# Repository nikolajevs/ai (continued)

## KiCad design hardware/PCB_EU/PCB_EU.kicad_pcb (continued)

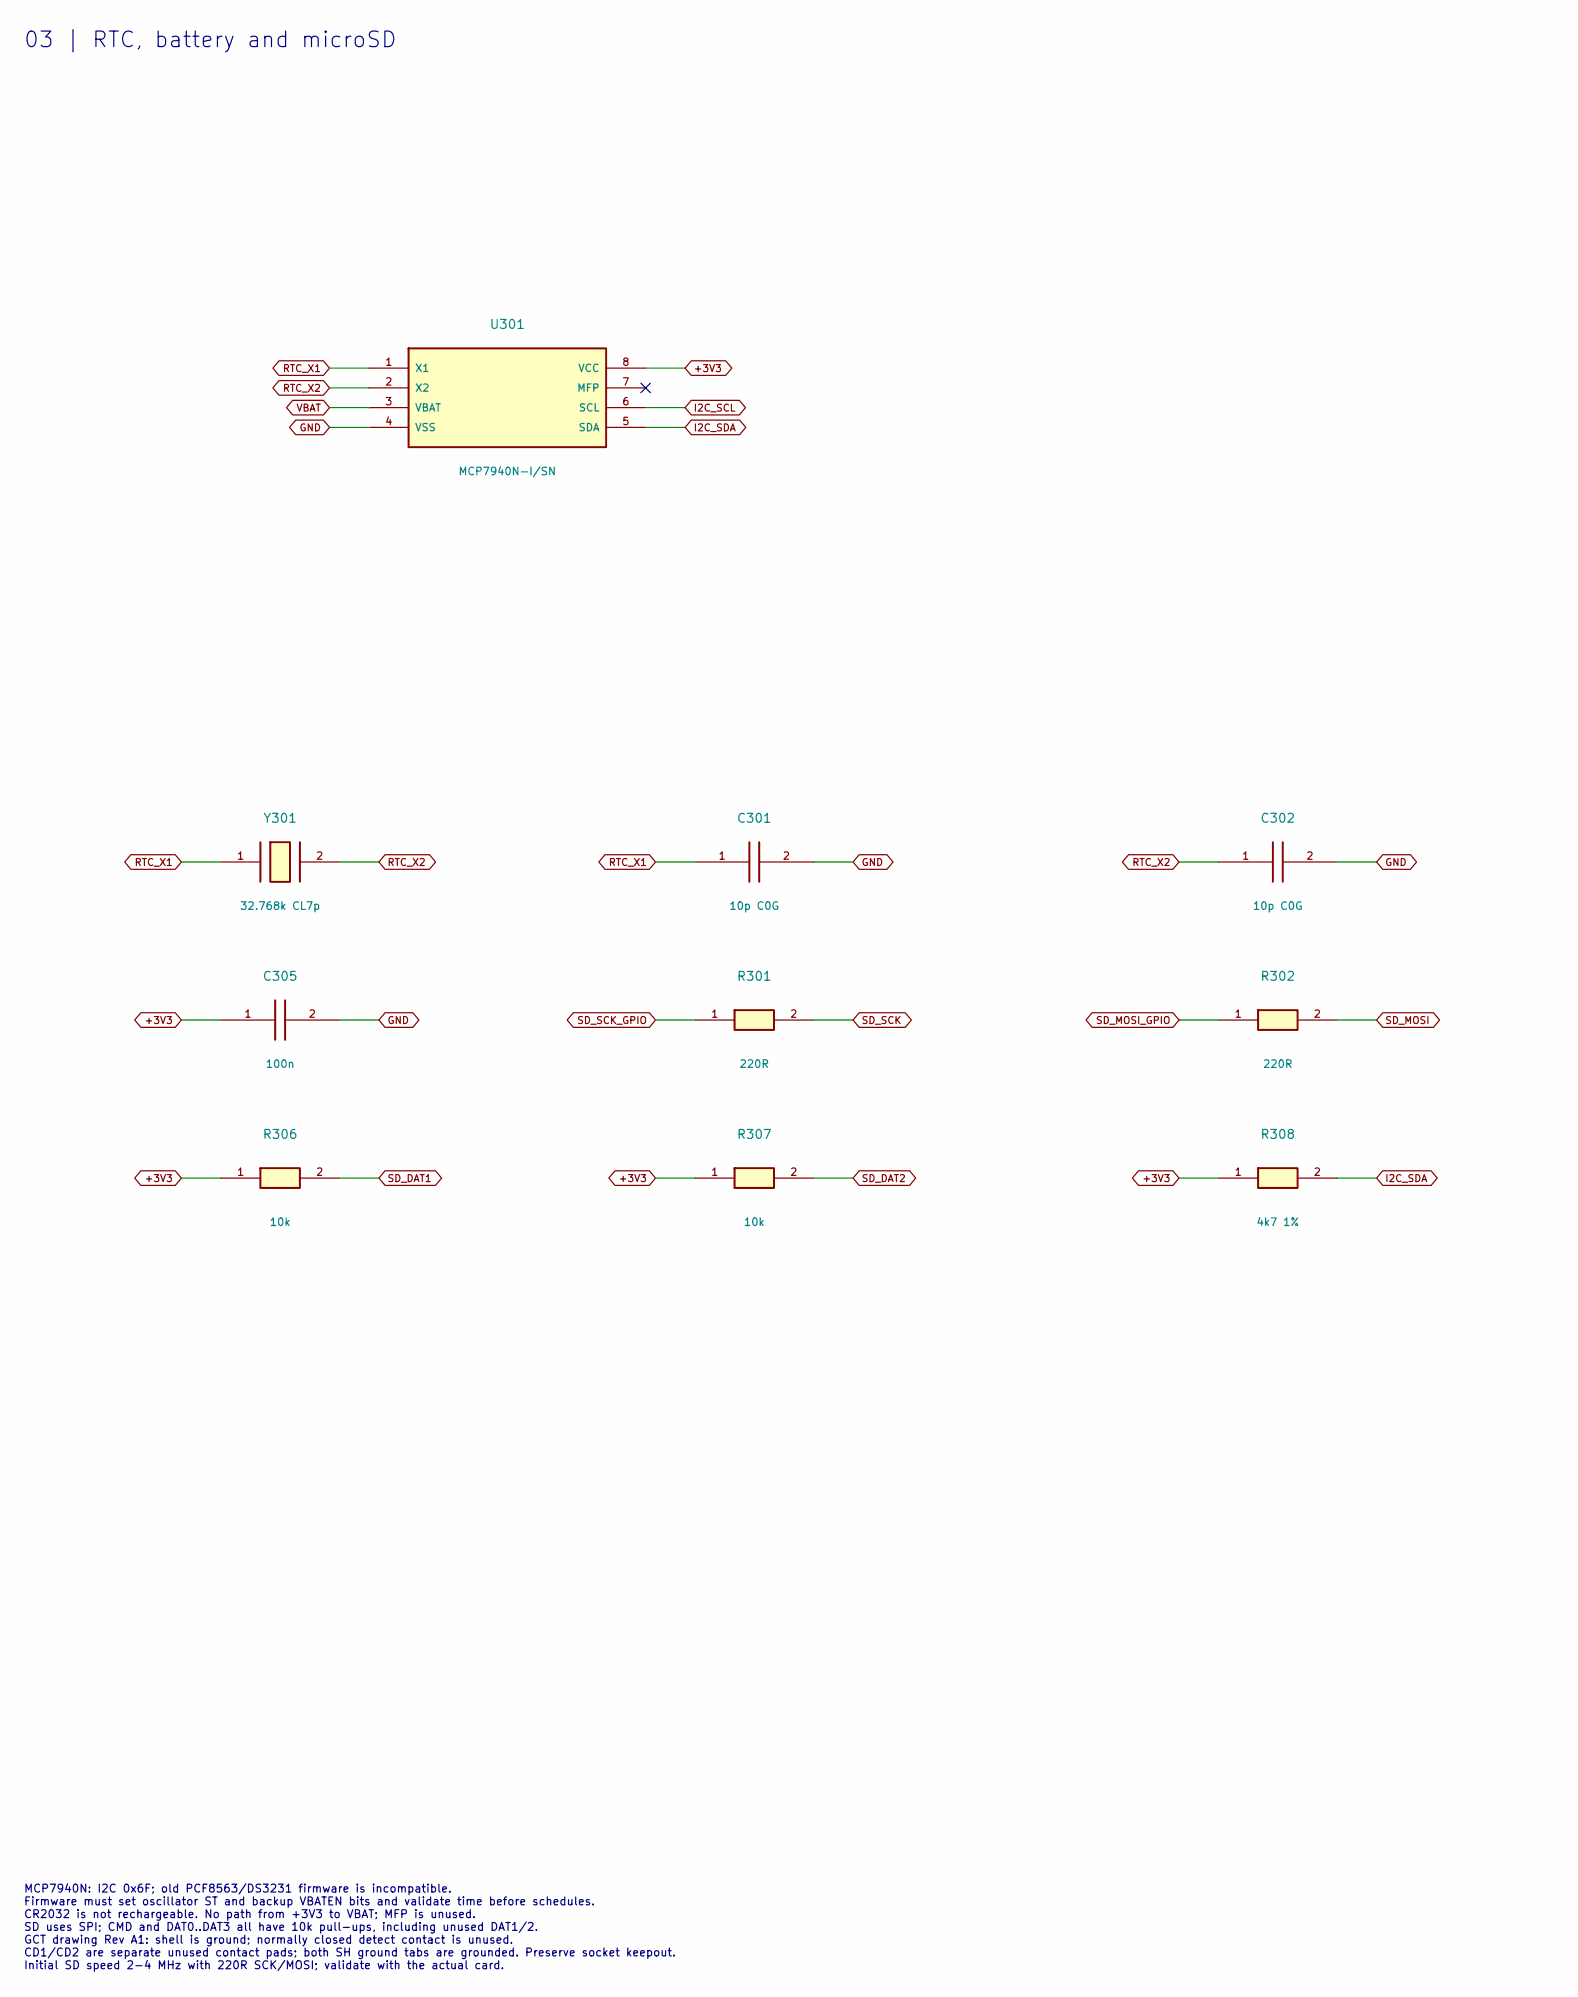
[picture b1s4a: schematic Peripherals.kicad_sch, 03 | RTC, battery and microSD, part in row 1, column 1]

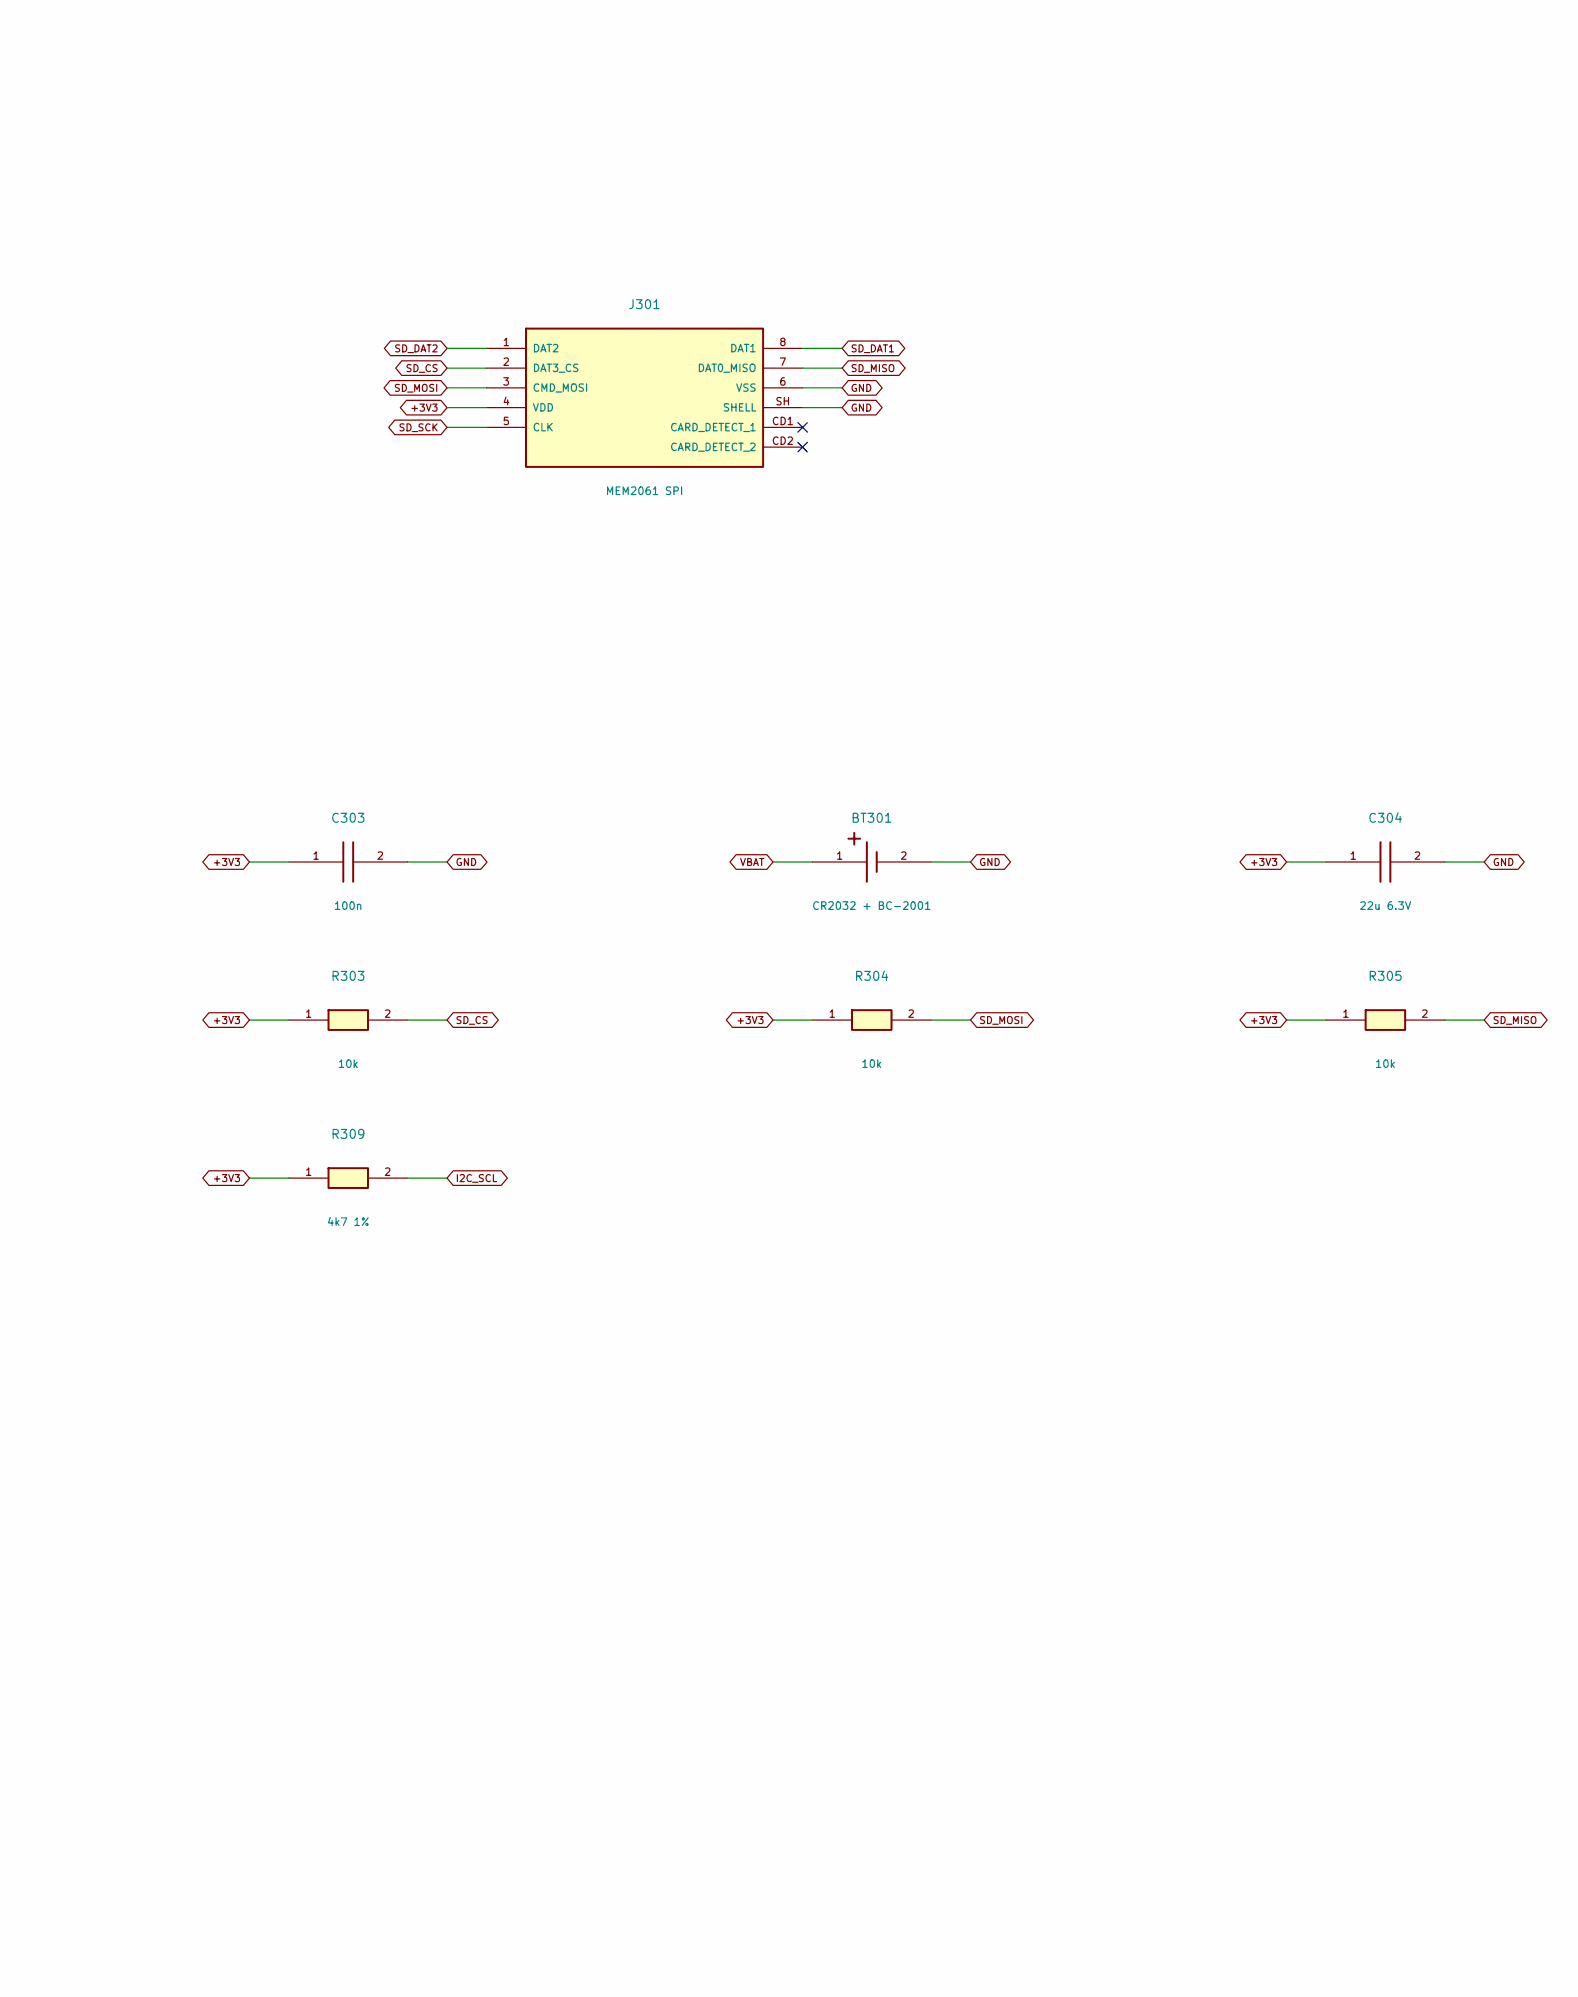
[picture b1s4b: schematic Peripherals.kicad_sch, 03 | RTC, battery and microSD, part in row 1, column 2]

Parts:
BT301: CR2032 + BC-2001; Battery_COMF_BC-2001; MPN BC-2001
C301, C302: 10p C0G; C_1206_3216Metric; MPN C1206C100J5GACTU
C303, C305: 100n; C_0805_2012Metric; MPN CL21B104KBCNNNC
C304: 22u 6.3V; C_1206_3216Metric; MPN CL31A226KQHNNNE
J301: MEM2061 SPI; microSD_GCT_MEM2061-01-188-00-A; MPN MEM2061-01-188-00-A
R301, R302: 220R; R_1206_3216Metric; MPN SMD1206-220R-1%
R303, R304, R305, R306, R307: 10k; R_0603_1608Metric; MPN SMD0603-10K
R308, R309: 4k7 1%; R_1206_3216Metric; MPN SMD1206 4K7 1%
U301: MCP7940N-I/SN; SOIC-8_3.9x4.9mm_P1.27mm; MPN MCP7940N-I/SN
Y301: 32.768k CL7p; Crystal_Abracon_ABS07; MPN ABS07-32.768KHZ-7-T

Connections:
+3V3: C303.1, C304.1, C305.1, J301.4 (VDD), R303.1, R304.1, R305.1, R306.1, R307.1, R308.1, R309.1, U301.8 (VCC); also elsewhere on the board
GND: BT301.2, C301.2, C302.2, C303.2, C304.2, C305.2, J301.6 (VSS), J301.SH (SHELL), U301.4 (VSS); also elsewhere on the board
I2C_SCL: R309.2, U301.6 (SCL); also elsewhere on the board
I2C_SDA: R308.2, U301.5 (SDA); also elsewhere on the board
RTC_X1: C301.1, U301.1 (X1), Y301.1
RTC_X2: C302.1, U301.2 (X2), Y301.2
SD_CS: J301.2 (DAT3_CS), R303.2; also elsewhere on the board
SD_DAT1: J301.8 (DAT1), R306.2
SD_DAT2: J301.1 (DAT2), R307.2
SD_MISO: J301.7 (DAT0_MISO), R305.2; also elsewhere on the board
SD_MOSI: J301.3 (CMD_MOSI), R302.2, R304.2
SD_MOSI_GPIO: R302.1; also elsewhere on the board
SD_SCK: J301.5 (CLK), R301.2
SD_SCK_GPIO: R301.1; also elsewhere on the board
VBAT: BT301.1, U301.3 (VBAT)

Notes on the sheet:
03 | RTC, battery and microSD
MCP7940N: I2C 0x6F; old PCF8563/DS3231 firmware is incompatible. Firmware must set oscillator ST and backup VBATEN bits and validate time before schedules. CR2032 is not rechargeable. No path from +3V3 to VBAT; MFP is unused. SD uses SPI; CMD and DAT0..DAT3 all have 10k pull-ups, including unused D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

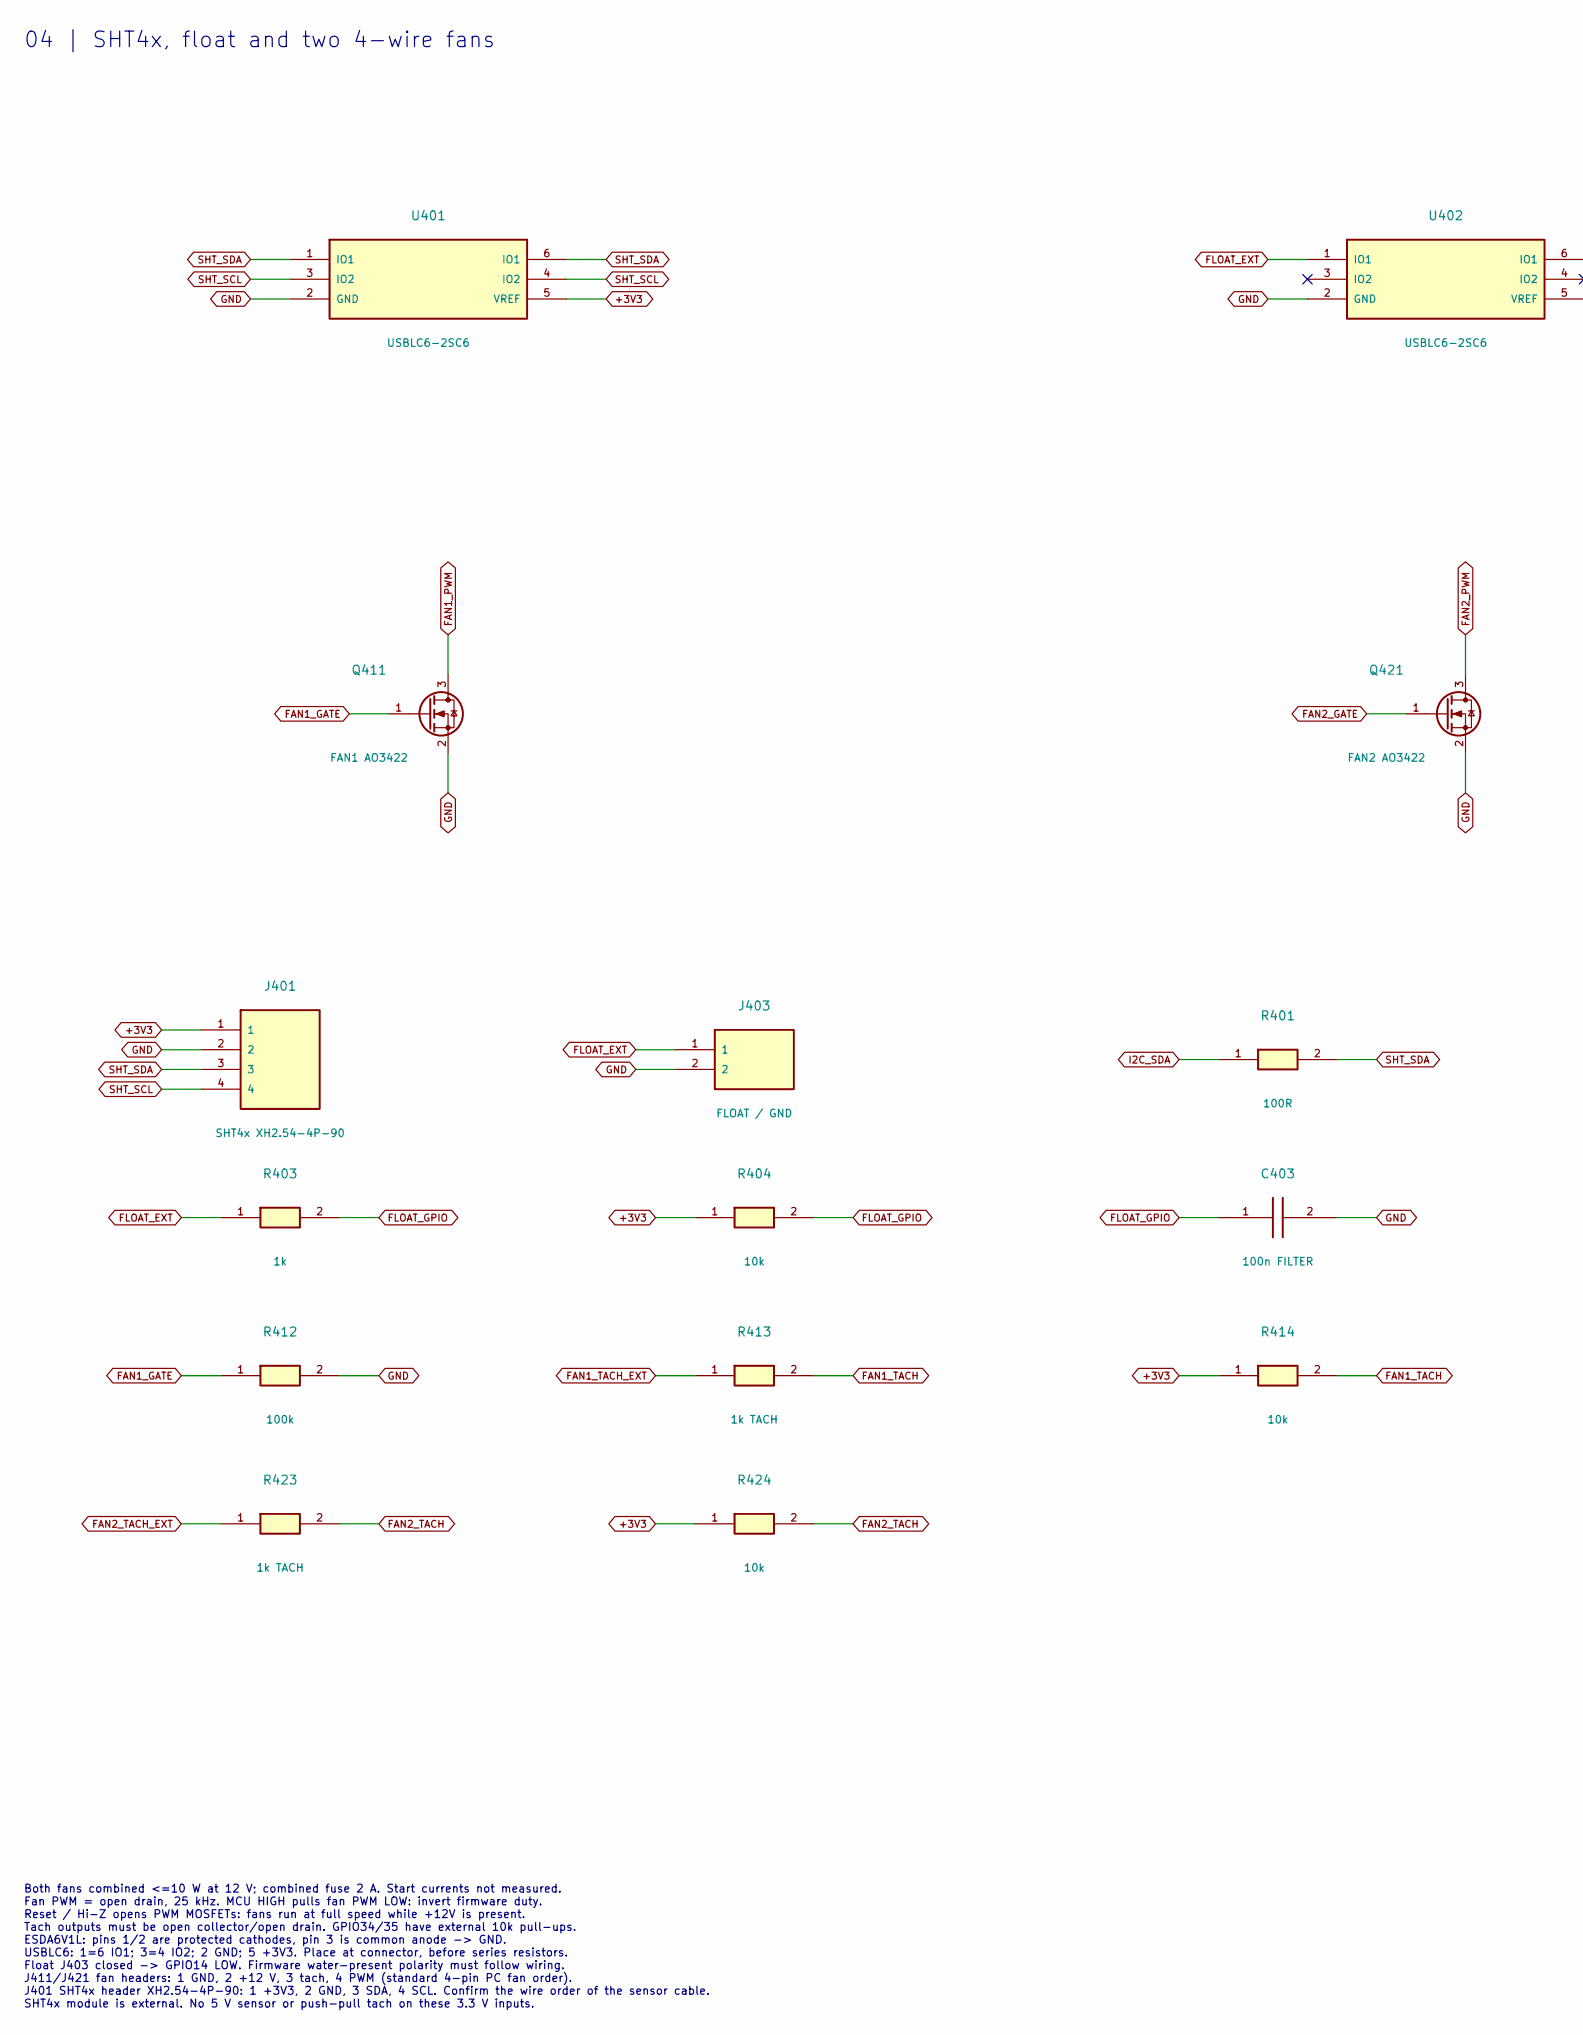
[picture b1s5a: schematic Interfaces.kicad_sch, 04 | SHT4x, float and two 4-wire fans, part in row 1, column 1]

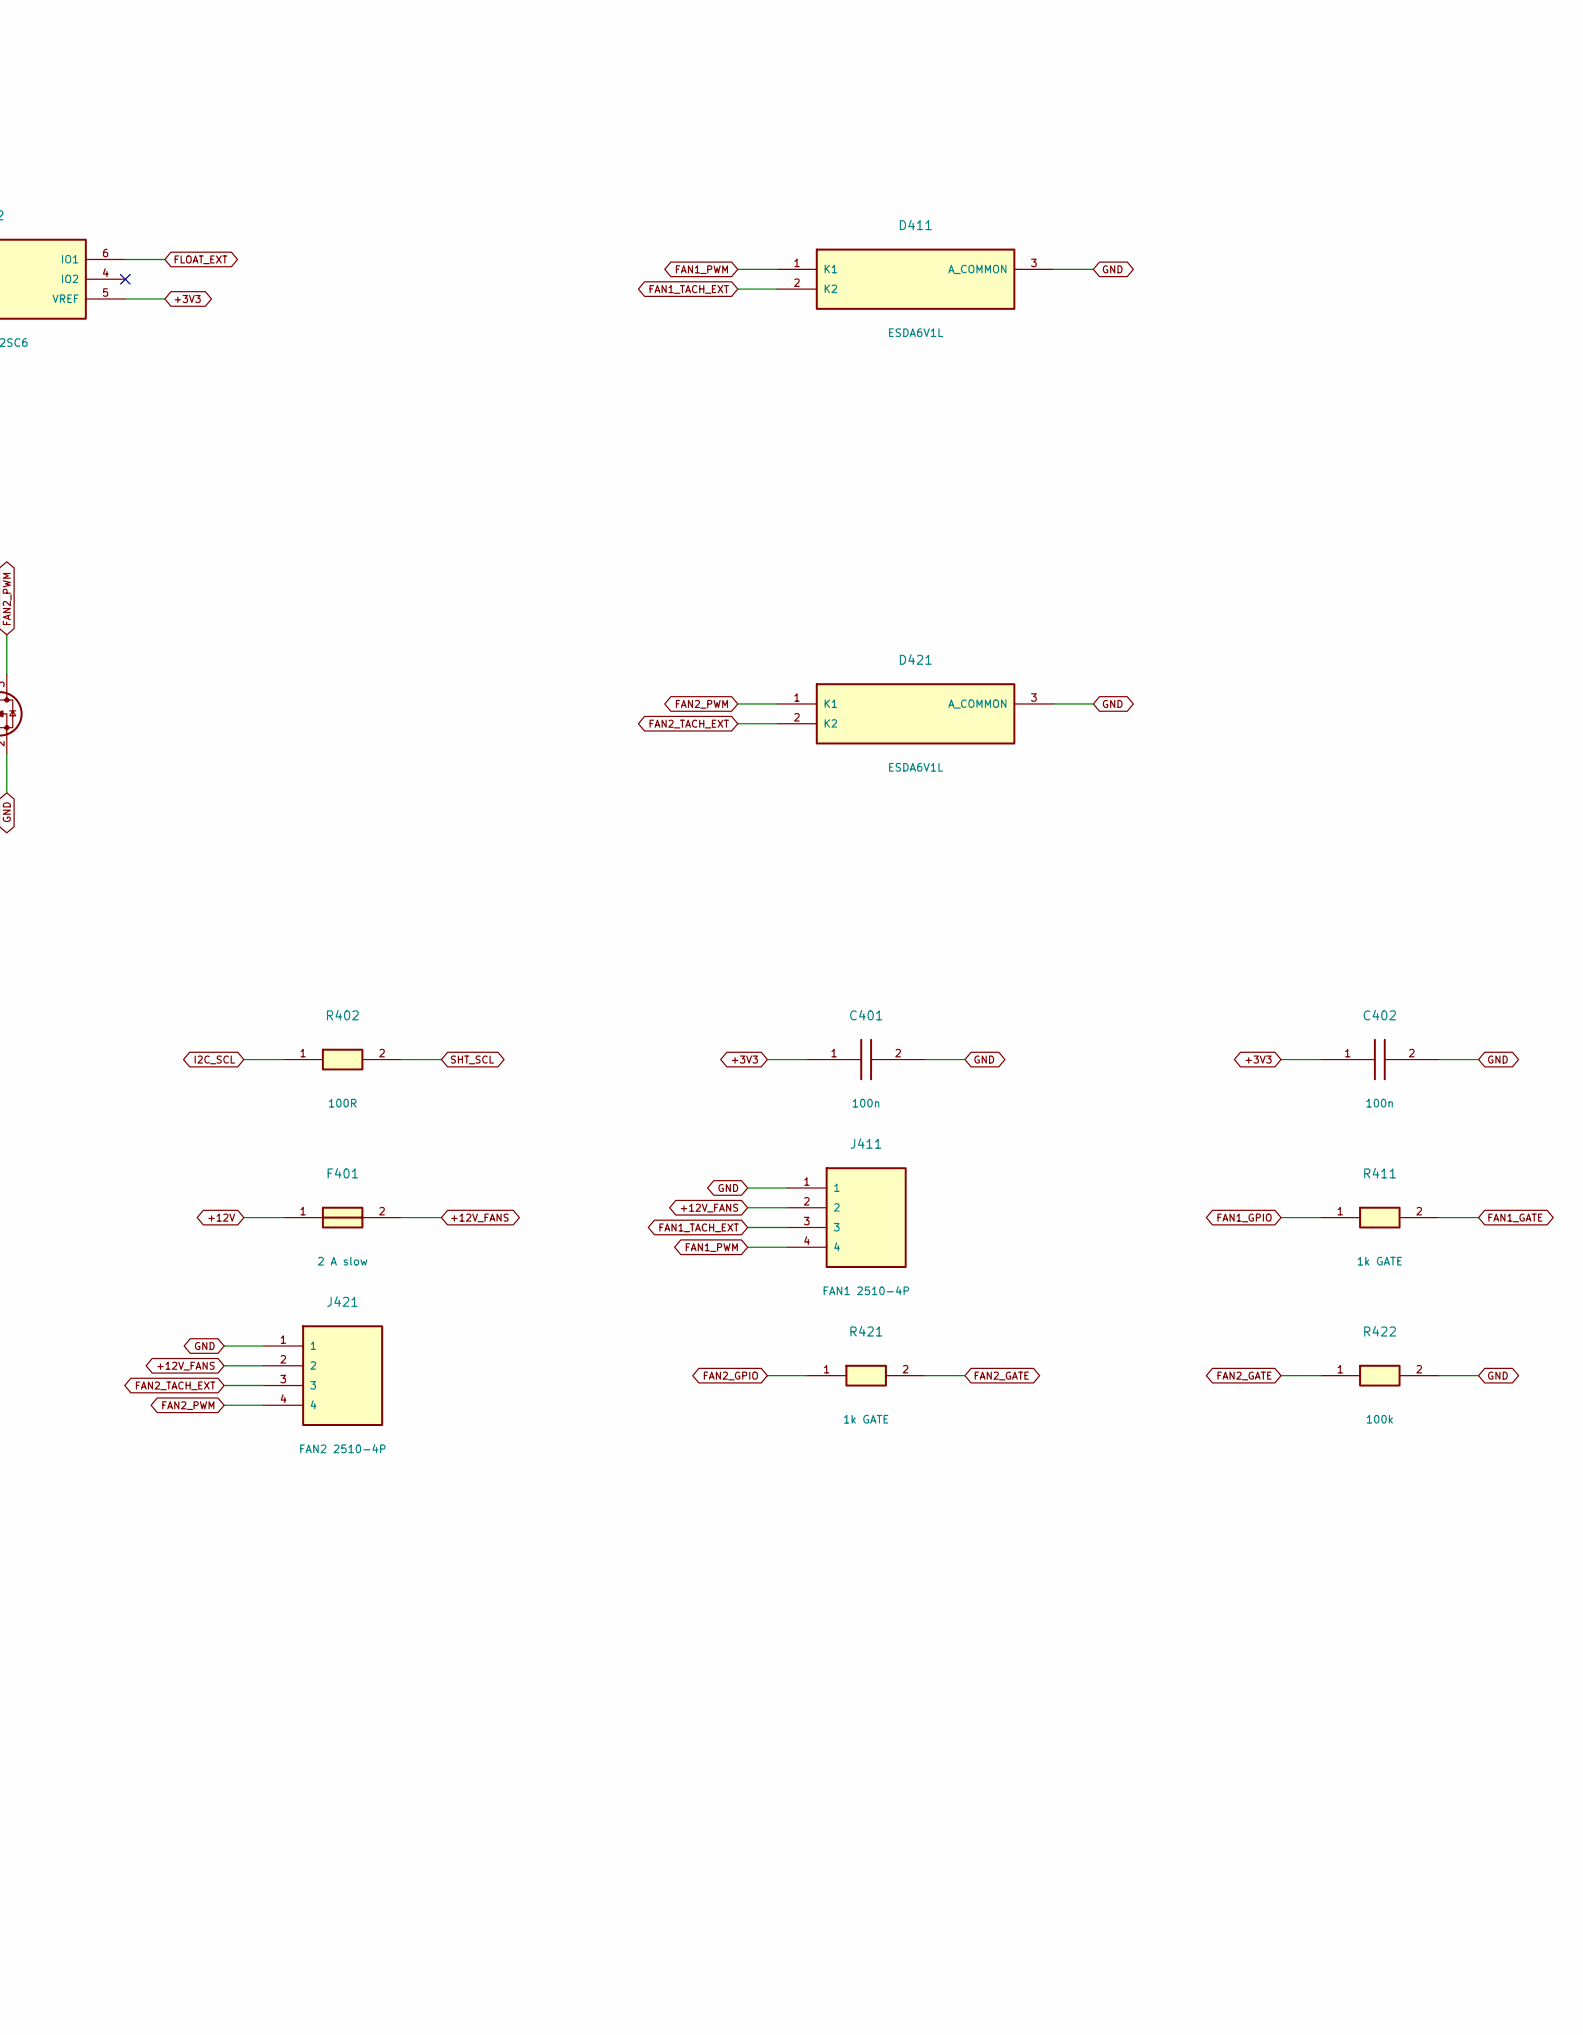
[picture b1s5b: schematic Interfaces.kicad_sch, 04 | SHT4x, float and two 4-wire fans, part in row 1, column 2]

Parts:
C401, C402: 100n; C_0805_2012Metric; MPN CL21B104KBCNNNC
C403: 100n FILTER; C_0805_2012Metric; MPN CL21B104KBCNNNC
D411, D421: ESDA6V1L; SOT-23; MPN ESDA6V1L
F401: 2 A slow; Fuse_Schurter_UMT250; MPN 3403.0169.11
J401: SHT4x XH2.54-4P-90; JST_XH_S4B-XH-A_1x04_P2.50mm_Horizontal; MPN XH2.54-4P-90
J403: FLOAT / GND; TerminalBlock_Degson_DG306-5.0_1x02; MPN DG306-5.0-2P12
J411: FAN1 2510-4P; Molex_KK-254_AE-6410-04A_1x04_P2.54mm_Vertical; MPN KF2510-4A
J421: FAN2 2510-4P; Molex_KK-254_AE-6410-04A_1x04_P2.54mm_Vertical; MPN KF2510-4A
Q411: FAN1 AO3422; SOT-23; MPN AO3422
Q421: FAN2 AO3422; SOT-23; MPN AO3422
R401, R402: 100R; R_1206_3216Metric; MPN SMD1206-100R-1%
R403: 1k; R_0603_1608Metric; MPN SMD0603-1K
R404, R414, R424: 10k; R_0603_1608Metric; MPN SMD0603-10K
R411, R421: 1k GATE; R_0603_1608Metric; MPN SMD0603-1K
R412, R422: 100k; R_0603_1608Metric; MPN SMD0603-100K
R413, R423: 1k TACH; R_0603_1608Metric; MPN SMD0603-1K
U401, U402: USBLC6-2SC6; SOT-23-6; MPN USBLC6-2SC6

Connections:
+3V3: C401.1, C402.1, J401.1, R404.1, R414.1, R424.1, U401.5 (VREF), U402.5 (VREF); also elsewhere on the board
+12V: F401.1; also elsewhere on the board
+12V_FANS: F401.2, J411.2, J421.2
FAN1_GATE: Q411.1 (G), R411.2, R412.1
FAN1_GPIO: R411.1; also elsewhere on the board
FAN1_PWM: D411.1 (K1), J411.4, Q411.3 (D)
FAN1_TACH: R413.2, R414.2; also elsewhere on the board
FAN1_TACH_EXT: D411.2 (K2), J411.3, R413.1
FAN2_GATE: Q421.1 (G), R421.2, R422.1
FAN2_GPIO: R421.1; also elsewhere on the board
FAN2_PWM: D421.1 (K1), J421.4, Q421.3 (D)
FAN2_TACH: R423.2, R424.2; also elsewhere on the board
FAN2_TACH_EXT: D421.2 (K2), J421.3, R423.1
FLOAT_EXT: J403.1, R403.1, U402.1 (IO1), U402.6 (IO1)
FLOAT_GPIO: C403.1, R403.2, R404.2; also elsewhere on the board
GND: C401.2, C402.2, C403.2, D411.3 (A_COMMON), D421.3 (A_COMMON), J401.2, J403.2, J411.1, J421.1, Q411.2 (S), Q421.2 (S), R412.2, R422.2, U401.2 (GND), U402.2 (GND); also elsewhere on the board
I2C_SCL: R402.1; also elsewhere on the board
I2C_SDA: R401.1; also elsewhere on the board
SHT_SCL: J401.4, R402.2, U401.3 (IO2), U401.4 (IO2)
SHT_SDA: J401.3, R401.2, U401.1 (IO1), U401.6 (IO1)

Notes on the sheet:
04 | SHT4x, float and two 4-wire fans
Both fans combined <=10 W at 12 V; combined fuse 2 A. Start currents not measured. Fan PWM = open drain, 25 kHz. MCU HIGH pulls fan PWM LOW: invert firmware duty. Reset / Hi-Z opens PWM MOSFETs: fans run at full speed while +12V is present. Tach outputs must be open collector/open drain. GPIO34/35 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
